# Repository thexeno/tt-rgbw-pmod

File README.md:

# tt-rgbw-pmod
An overkill PMOD to handle an RGBW LED for experimenting with the color rendering of the [thexeno/tt08-rgbw-controller](https://github.com/thexeno/tt08-rgbw-controller/ "tt08-rgbw-controller") ASIC. 
This PMOD matches with the [TinyTapeout/tt-demo-pcb](https://github.com/TinyTapeout/tt-demo-pcb "tt-demo-pcb"). These links are referred to as the "ASIC documentation".

### <p align="center"> PREVIEW: https://www.youtube.com/watch?v=X-74kIeId4A </p>

  <div align="center">

  <br>
  </div>

## Overview

This PMOD board provides high-power LED driver capabilities for the tt08-rgbw-controller ASIC, featuring four independent channels for RGBW LED control with both digital PWM and analog dimming modes.

## Pinout

### PWM inputs (inputs PMOD side, outputs ASIC side)

| Pmod    | TinyTapeout | Function        | Note                  |
|---------|-------------|-----------------|-----------------------|
| OUTPUT1 | uo[0]       | Red PWM input   | Input impedance 100 kΩ|
| OUTPUT2 | uo[1]       | Green PWM input | Input impedance 100 kΩ|
| OUTPUT3 | uo[2]       | Blue PWM input  | Input impedance 100 kΩ|
| OUTPUT4 | uo[3]       | White PWM input | Input impedance 100 kΩ|
| OUTPUT5 - 8   | uo[4:7]           | Not connected   |                       |

### Inputs ASIC side

All "INPUT" pins are disconnected on the PMOD, not used. But the ASIC and the Demoboard are using them for the SPI communication, so signals are present if probed. See ASIC documentation.

### Colorwheel Debug Port

This applies only if enabled, see ASIC documentation.

| Pmod    | TinyTapeout | Function        | Note                  |
|---------|-------------|-----------------|-----------------------|
| BIDIR1 | uio_out[0]       | CwPU register bit 0   |  |
| BIDIR2 | uio_out[1]       | CwPU register bit 1 | |
| BIDIR3 | uio_out[2]       | CwPU register bit 2  | |
| BIDIR4 | uio_out[3]       | CwPU register bit 3 | |
| BIDIR5    | uio_out[4]           | CwPU register bit 4   |                       |
| BIDIR6    | uio_out[5]           | CwPU register bit 5   |                       |
| BIDIR7    | uio_out[6]           | CwPU register bit 6   |                       |
| BIDIR8    | uio_out[7]           | CwPU register bit 7   |                       |

## Getting Started

### Quick Setup Checklist

1. Select the control mode for each color channel using jumpers JP1–JP4:
  - Jumper bridged: Analog (LED-side) dimming mode
  - Jumper open: Digital (LED-side) PWM mode
2. Verify 3.3V power is available on the Demoboard's PMOD connector.
3. Connect the RGBW Color Processor board to the Demoboard.
4. Apply external power: Connect 6–20V to J4 or J5 (minimum 5V required to activate drivers).

### Using External LEDs

To use external LEDs instead of the onboard ones, open the following jumper connections:
- R3, R4, R5, R8, R9, R10, R11, R12

### Current Adjustment

Adjust the constant-current output via resistors:
- R14 (Red channel)
- R18 (Green channel)
- R22 (Blue channel)
- R26 (White channel)

Current calculation:
- Digital dimming mode: I = 0.1V / R (default: 75 mA)
- Analog dimming mode: I = 0.2V / R (default: 150 mA)

## Operating Modes

### Digital PWM Mode (Jumper Open)
- PWM PMOD pin frequency: < 1 kHz
- Lower current consumption
- Suitable for most applications

### Analog Dimming Mode (Jumper Bridged)
- PWM PMOD pin frequency: > 10 kHz (recommended: 50 kHz)
- Higher current capability
- For continuous operation at default settings (150 mA per channel), a small heatsink is recommended:
  - Base size: 7×7 mm
  - Thermal resistance: 30–40 °C/W
 
## Debugging Features

Breakout to CwPU protocol 8-bit interface for internal registers probing. This is active only if enabled. See ASIC documentation.

## Electrical Characteristics

| Parameter                                      | Min | Typ | Max | Unit | Notes                      |
|-----------------------------------------------|-----|-----|-----|------|----------------------------|
| External supply voltage                        | 6   | 12  | 20  | V    | Required (J4 or J5)        |
| External supply current                        | -   | -   | 400 | mA  | 2W total max               |
| PMOD Logic VDD                        | 3.0   | -   | 5.0 | V  | To handle correctly analog or digital dimming detection               |
| Logic input voltage                            | -   | 3.3 | -   | V    | TTL compatible             |
| LED current (Digital mode)                     | -   | 75  | -   | mA   | Per channel, default       |
| LED current (Analog mode)                      | -   | 150 | -   | mA   | Per channel, default       |
| PWM input for Digital mode           | -   | -   | 1   | kHz  | Maximum recommended        |
| PWM input for Analog mode            | 10  | 50  | -   | kHz  | Minimum / recommended      |
| V<sub>IL</sub>                                     | -  | 0.8  | - | V  | LVTTL     |
| V<sub>IH</sub>                                       | -  | 2.0  | - | V  | LVTTL     |

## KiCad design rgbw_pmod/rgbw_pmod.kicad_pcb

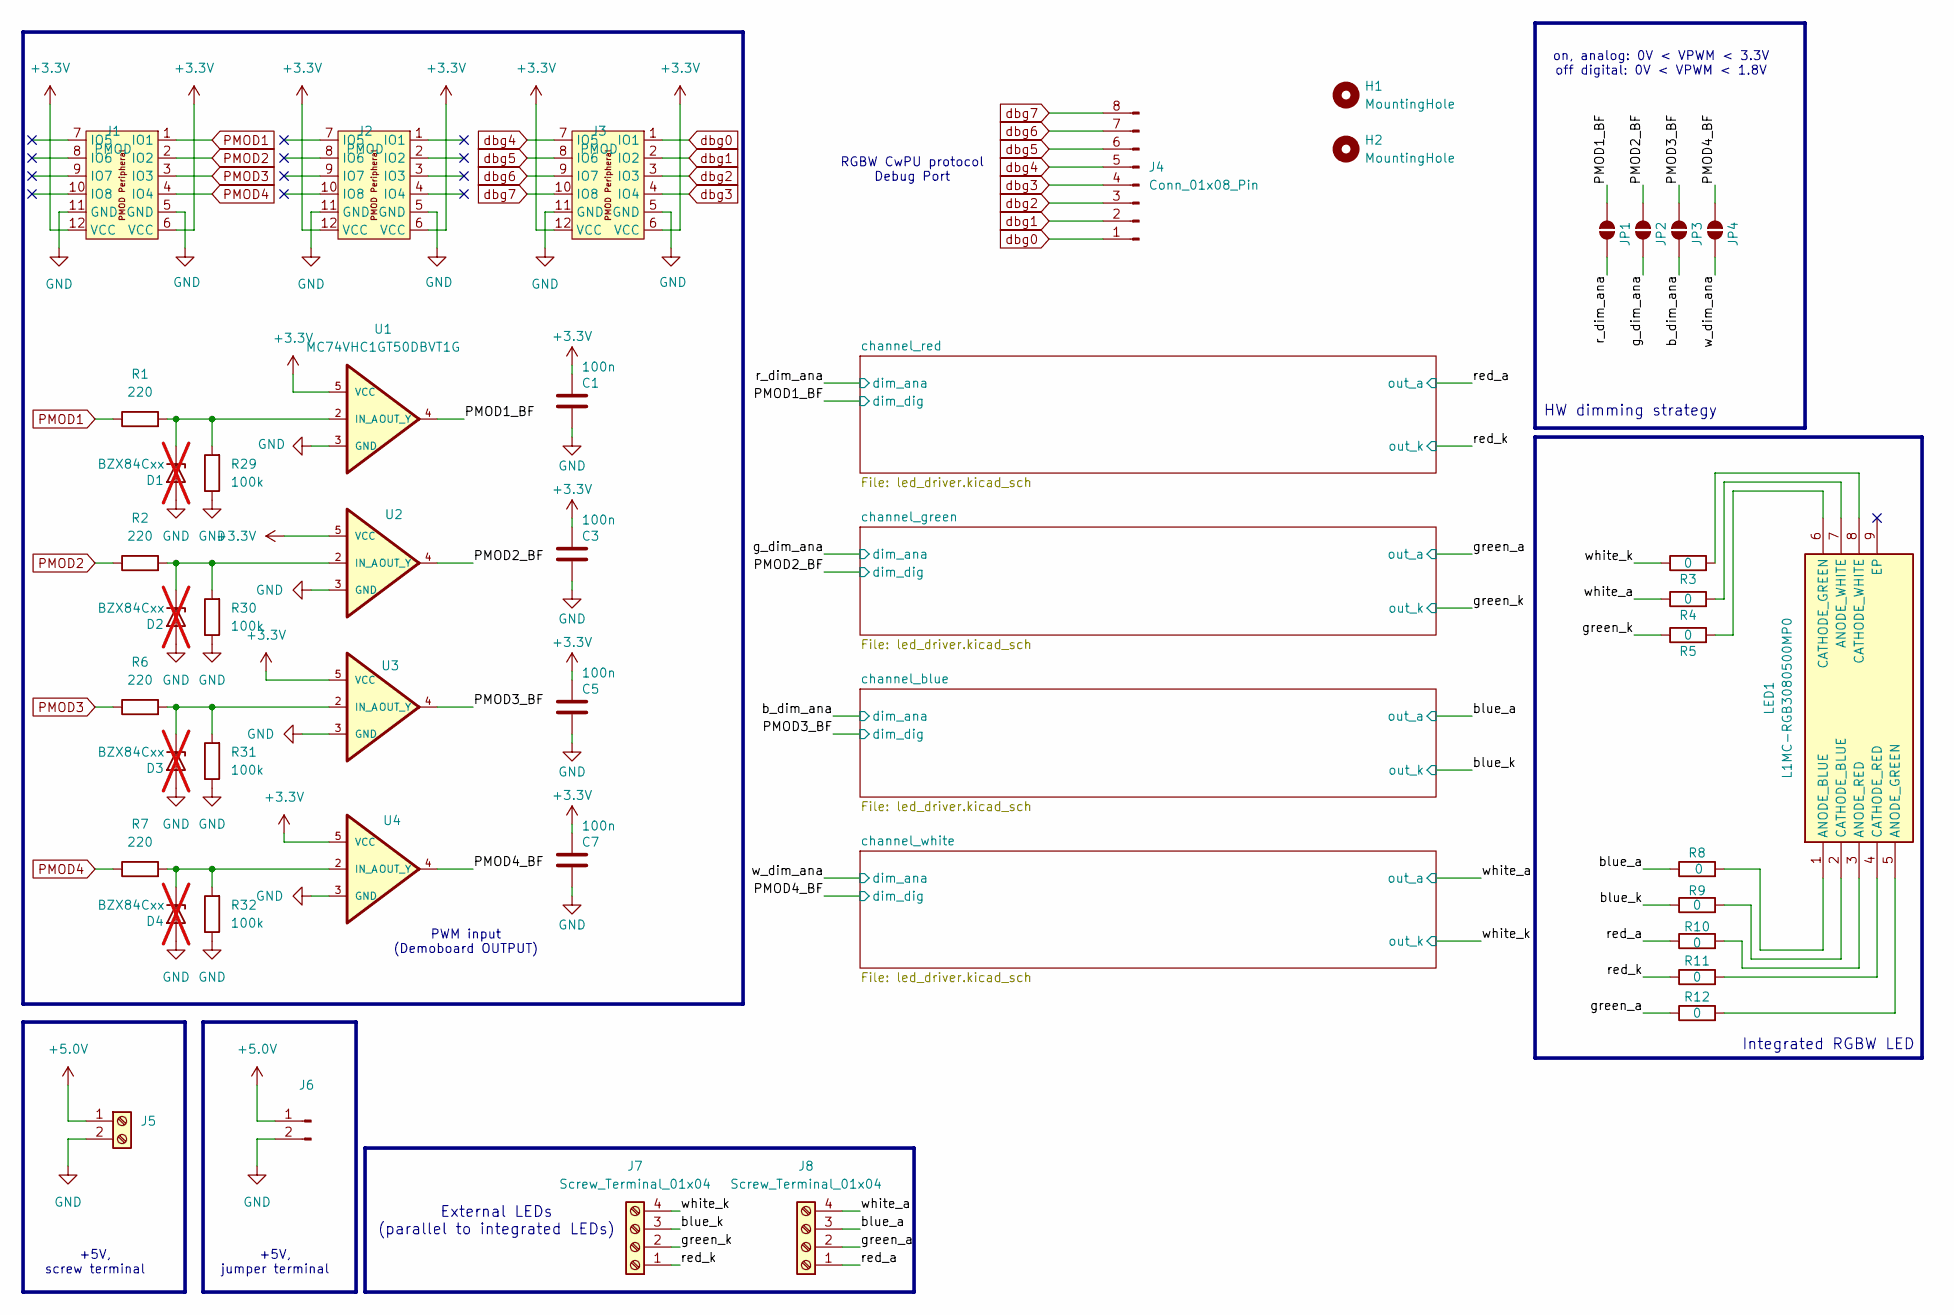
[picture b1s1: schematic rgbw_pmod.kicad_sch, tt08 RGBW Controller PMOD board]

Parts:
C1, C3, C5, C7: 100n; C_0603_1608Metric_Pad1.08x0.95mm_HandSolder
D1, D2, D3, D4: BZX84Cxx; SOT-23-3; not fitted
H1, H2: MountingHole; MountingHole_3.2mm_M3_ISO7380
J1, J2, J3: PMOD; PinHeader_2x06_P2.54mm_PMODPeriph2B; MPN 826634-6; LCSC C2935938
J4: Conn_01x08_Pin; PinHeader_1x08_P2.54mm_Vertical
J5: Screw_Terminal_01x02; TerminalBlock_Altech_AK300-2_P5.00mm
J6: Conn_01x02_Pin; PinHeader_1x02_P2.54mm_Vertical
J7, J8: Screw_Terminal_01x04; Altech_AK100_1x04_P5.00mm
JP1, JP2, JP3, JP4: SolderJumper_2_Open; SolderJumper-2_P1.3mm_Open_TrianglePad1.0x1.5mm
LED1: L1MC-RGB3080500MP0; L1MCRGB3080500MP0; Mouser Part Number 997-L1MCRGB3080500MP
R1, R2, R6, R7: 220; R_0603_1608Metric_Pad0.98x0.95mm_HandSolder
R3, R4, R5, R8, R9, R10, R11, R12: 0; R_0603_1608Metric_Pad0.98x0.95mm_HandSolder
R29, R30, R31, R32: 100k; R_0603_1608Metric_Pad0.98x0.95mm_HandSolder
U1, U2, U3, U4: MC74VHC1GT50DBVT1G; SOT95P275X110-5N; MPN MC74VHC1GT50DTT1

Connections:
+3.3V: C1.1, C3.1, C5.1, C7.1, J1.6 (VCC), J1.12 (VCC), J2.6 (VCC), J2.12 (VCC), J3.6 (VCC), J3.12 (VCC), U1.5 (VCC), U2.5 (VCC), U3.5 (VCC), U4.5 (VCC)
+5.0V: J5.1, J6.1; also elsewhere on the board
/PMOD1_BF: JP1.2 (B), U1.4 (OUT_Y); also elsewhere on the board
/PMOD2_BF: JP2.2 (B), U2.4 (OUT_Y); also elsewhere on the board
/PMOD3_BF: JP3.2 (B), U3.4 (OUT_Y); also elsewhere on the board
/PMOD4_BF: JP4.2 (B), U4.4 (OUT_Y); also elsewhere on the board
/b_dim_ana: JP3.1 (A); also elsewhere on the board
/blue_a: J8.3, R8.1; also elsewhere on the board
/blue_k: J7.3, R9.1; also elsewhere on the board
/g_dim_ana: JP2.1 (A); also elsewhere on the board
/green_a: J8.2, R12.1; also elsewhere on the board
/green_k: J7.2, R5.1; also elsewhere on the board
/r_dim_ana: JP1.1 (A); also elsewhere on the board
/red_a: J8.1, R10.1; also elsewhere on the board
/red_k: J7.1, R11.1; also elsewhere on the board
/w_dim_ana: JP4.1 (A); also elsewhere on the board
/white_a: J8.4, R4.1; also elsewhere on the board
/white_k: J7.4, R3.1; also elsewhere on the board
GND: C1.2, C3.2, C5.2, C7.2, D1.1 (A), D2.1 (A), D3.1 (A), D4.1 (A), J1.5 (GND), J1.11 (GND), J2.5 (GND), J2.11 (GND), J3.5 (GND), J3.11 (GND), J5.2, J6.2, R29.1, R30.1, R31.1, R32.1, U1.3 (GND), U2.3 (GND), U3.3 (GND), U4.3 (GND); also elsewhere on the board
unnamed: D1.3 (K), R1.2, R29.2, U1.2 (IN_A)
unnamed: D2.3 (K), R2.2, R30.2, U2.2 (IN_A)
unnamed: D3.3 (K), R6.2, R31.2, U3.2 (IN_A)
unnamed: D4.3 (K), R7.2, R32.2, U4.2 (IN_A)
unnamed: LED1.1 (ANODE_BLUE), R8.2
unnamed: LED1.5 (ANODE_GREEN), R12.2
unnamed: LED1.3 (ANODE_RED), R10.2
unnamed: LED1.7 (ANODE_WHITE), R4.2
unnamed: LED1.2 (CATHODE_BLUE), R9.2
unnamed: LED1.6 (CATHODE_GREEN), R5.2
unnamed: LED1.4 (CATHODE_RED), R11.2
unnamed: LED1.8 (CATHODE_WHITE), R3.2
PMOD1: J1.1 (IO1), R1.1
PMOD2: J1.2 (IO2), R2.1
PMOD3: J1.3 (IO3), R6.1
PMOD4: J1.4 (IO4), R7.1
dbg0: J3.1 (IO1), J4.1
dbg1: J3.2 (IO2), J4.2
dbg2: J3.3 (IO3), J4.3
dbg3: J3.4 (IO4), J4.4
dbg4: J3.7 (IO5), J4.5
dbg5: J3.8 (IO6), J4.6
dbg6: J3.9 (IO7), J4.7
dbg7: J3.10 (IO8), J4.8

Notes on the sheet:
on, analog: 0V < VPWM < 3.3V off digital: 0V < VPWM < 1.8V
Integrated RGBW LED
+5V, screw terminal
External LEDs (parallel to integrated LEDs)
PWM input (Demoboard OUTPUT)
+5V, jumper terminal
HW dimming strategy
RGBW CwPU protocol Debug Port

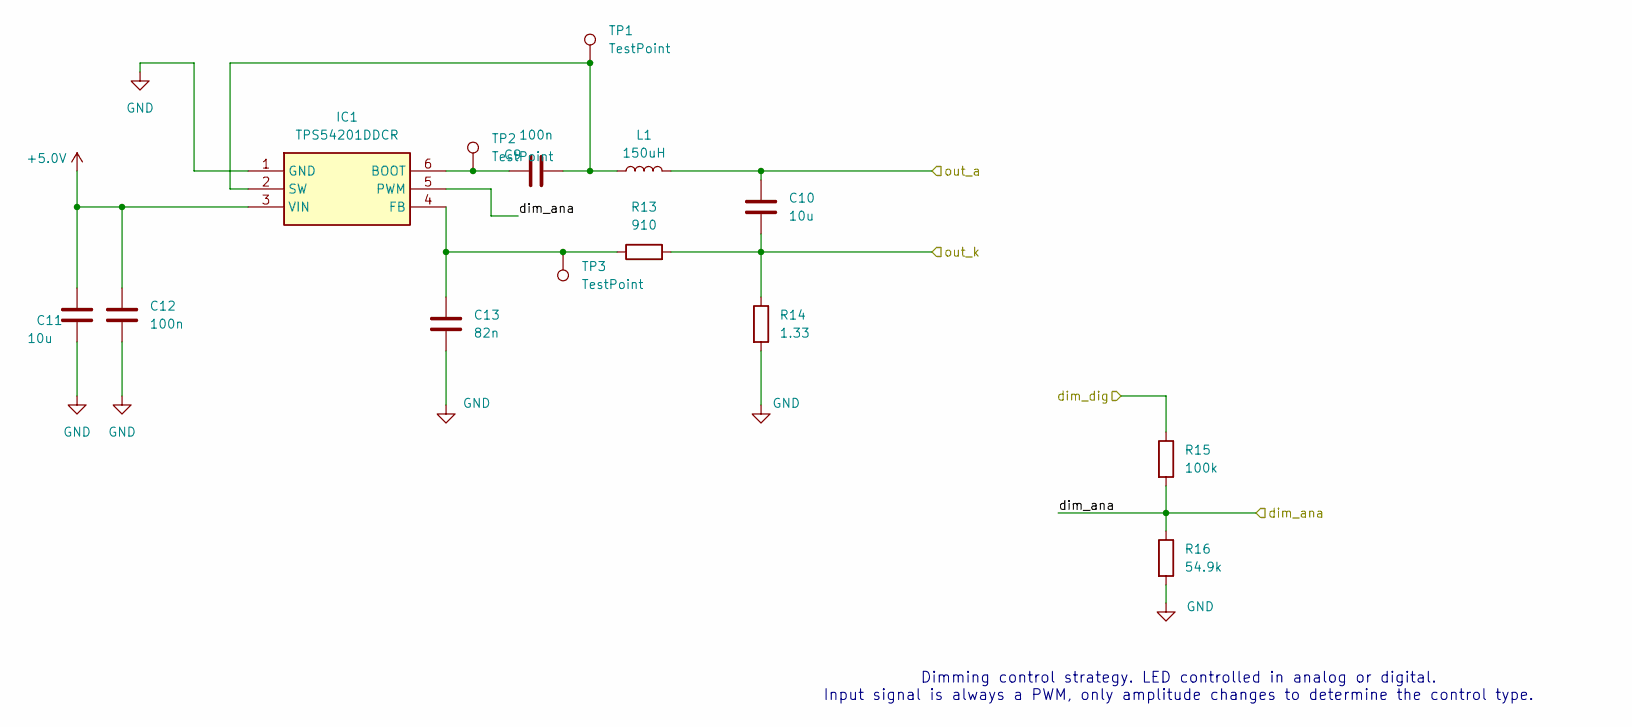
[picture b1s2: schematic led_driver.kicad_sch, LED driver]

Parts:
C9, C12: 100n; C_0603_1608Metric_Pad1.08x0.95mm_HandSolder
C10, C11: 10u; C_0805_2012Metric_Pad1.18x1.45mm_HandSolder
C13: 82n; C_0603_1608Metric_Pad1.08x0.95mm_HandSolder
IC1: TPS54201DDCR; SOT95P280X110-6N; Mouser Part Number 595-TPS54201DDCR
L1: 150uH; IND_BOURNS_SRR5028
R13: 910; R_0603_1608Metric_Pad0.98x0.95mm_HandSolder
R14: 1.33; R_0805_2012Metric_Pad1.20x1.40mm_HandSolder
R15: 100k; R_0603_1608Metric_Pad0.98x0.95mm_HandSolder
R16: 54.9k; R_0603_1608Metric_Pad0.98x0.95mm_HandSolder
TP1: TestPoint; TestPoint_Pad_D1.0mm
TP2, TP3: TestPoint; TestPoint_Keystone_5015_Micro_Mini

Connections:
+5.0V: C11.1, C12.1, IC1.3 (VIN); also elsewhere on the board
/PMOD1_BF: R15.1; also elsewhere on the board
/r_dim_ana: IC1.5 (PWM), R15.2, R16.1; also elsewhere on the board
/red_a: C10.1, L1.2; also elsewhere on the board
/red_k: C10.2, R13.2, R14.1; also elsewhere on the board
GND: C11.2, C12.2, C13.1, IC1.1 (GND), R14.2, R16.2; also elsewhere on the board
unnamed: C9.1, IC1.6 (BOOT), TP2.1
unnamed: C13.2, IC1.4 (FB), R13.1, TP3.1
unnamed: C9.2, IC1.2 (SW), L1.1, TP1.1

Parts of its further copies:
C14, C17, C19, C22, C24, C27: 100n; C_0603_1608Metric_Pad1.08x0.95mm_HandSolder
C15, C16, C20, C21, C25, C26: 10u; C_0805_2012Metric_Pad1.18x1.45mm_HandSolder
C18, C23, C28: 82n; C_0603_1608Metric_Pad1.08x0.95mm_HandSolder
IC2, IC3, IC4: TPS54201DDCR; SOT95P280X110-6N; Mouser Part Number 595-TPS54201DDCR
L2, L3, L4: 150uH; IND_BOURNS_SRR5028
R17, R21, R25: 910; R_0603_1608Metric_Pad0.98x0.95mm_HandSolder
R18, R22, R26: 1.33; R_0805_2012Metric_Pad1.20x1.40mm_HandSolder
R19, R23, R27: 100k; R_0603_1608Metric_Pad0.98x0.95mm_HandSolder
R20, R24, R28: 54.9k; R_0603_1608Metric_Pad0.98x0.95mm_HandSolder
TP5, TP9, TP13: TestPoint; TestPoint_Pad_D1.0mm
TP6, TP7, TP10, TP11, TP14, TP15: TestPoint; TestPoint_Keystone_5015_Micro_Mini

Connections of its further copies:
+5.0V: C16.1, C17.1, C21.1, C22.1, C26.1, C27.1, IC2.3 (VIN), IC3.3 (VIN), IC4.3 (VIN); also elsewhere on the board
/PMOD2_BF: R19.1; also elsewhere on the board
/PMOD3_BF: R23.1; also elsewhere on the board
/PMOD4_BF: R27.1; also elsewhere on the board
/b_dim_ana: IC3.5 (PWM), R23.2, R24.1; also elsewhere on the board
/blue_a: C20.1, L3.2; also elsewhere on the board
/blue_k: C20.2, R21.2, R22.1; also elsewhere on the board
/g_dim_ana: IC2.5 (PWM), R19.2, R20.1; also elsewhere on the board
/green_a: C15.1, L2.2; also elsewhere on the board
/green_k: C15.2, R17.2, R18.1; also elsewhere on the board
/w_dim_ana: IC4.5 (PWM), R27.2, R28.1; also elsewhere on the board
/white_a: C25.1, L4.2; also elsewhere on the board
/white_k: C25.2, R25.2, R26.1; also elsewhere on the board
GND: C16.2, C17.2, C18.1, C21.2, C22.2, C23.1, C26.2, C27.2, C28.1, IC2.1 (GND), IC3.1 (GND), IC4.1 (GND), R18.2, R20.2, R22.2, R24.2, R26.2, R28.2; also elsewhere on the board
unnamed: C14.1, IC2.6 (BOOT), TP6.1
unnamed: C18.2, IC2.4 (FB), R17.1, TP7.1
unnamed: C14.2, IC2.2 (SW), L2.1, TP5.1
unnamed: C19.1, IC3.6 (BOOT), TP10.1
unnamed: C23.2, IC3.4 (FB), R21.1, TP11.1
unnamed: C19.2, IC3.2 (SW), L3.1, TP9.1
unnamed: C24.1, IC4.6 (BOOT), TP14.1
unnamed: C28.2, IC4.4 (FB), R25.1, TP15.1
unnamed: C24.2, IC4.2 (SW), L4.1, TP13.1

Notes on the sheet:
Dimming control strategy. LED controlled in analog or digital. Input signal is always a PWM, only amplitude changes to determine the control type.

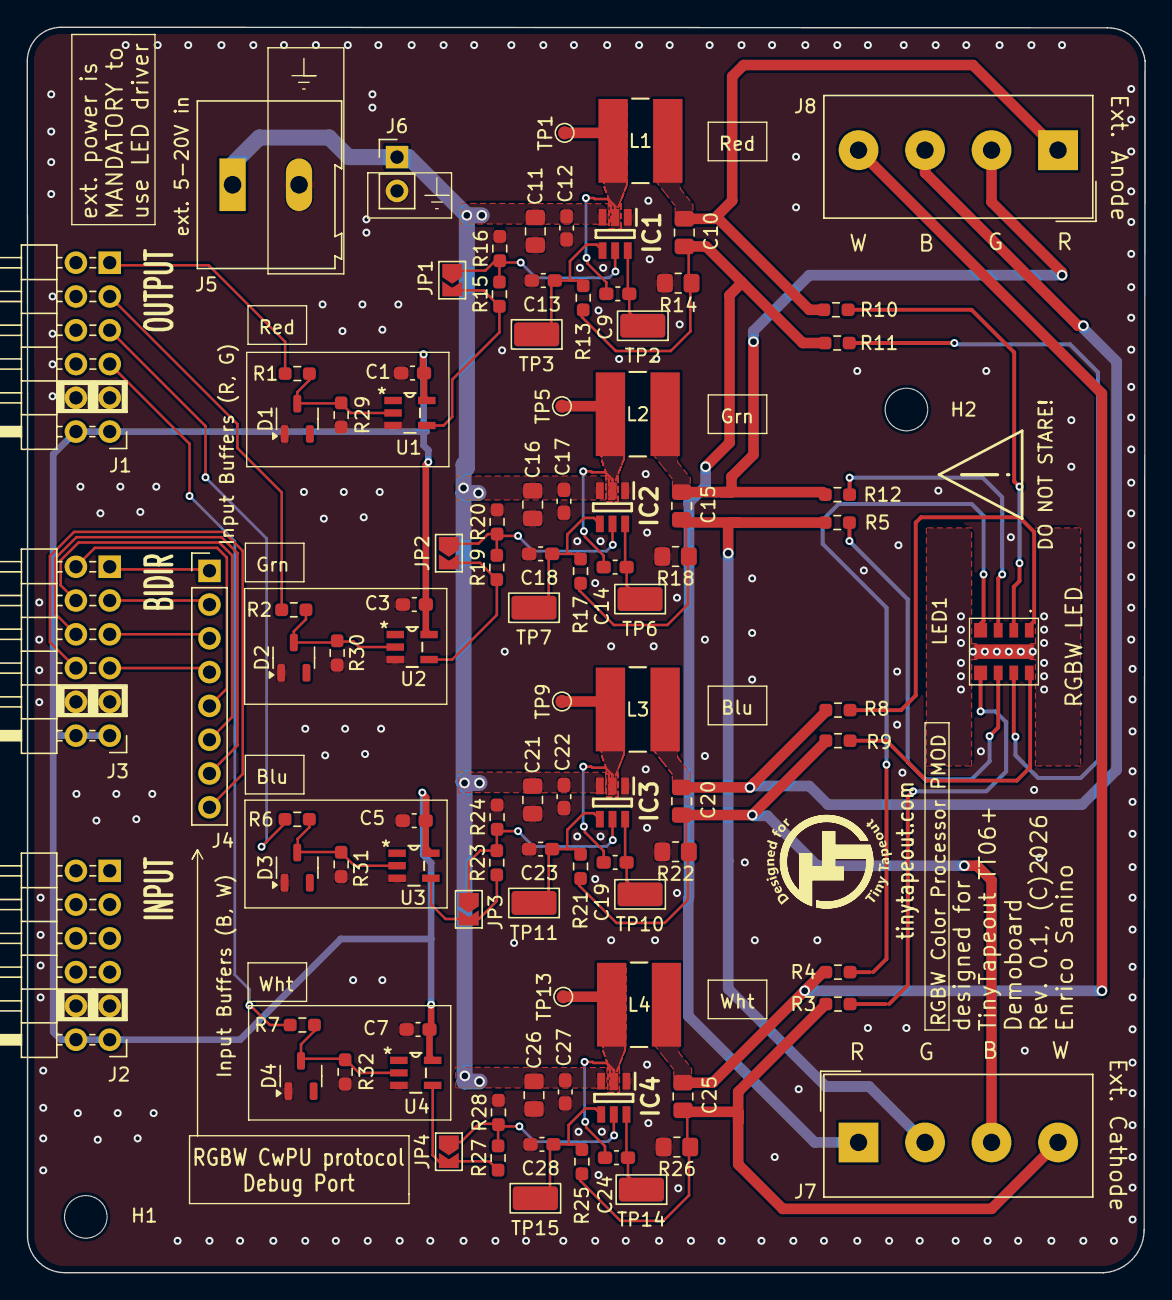
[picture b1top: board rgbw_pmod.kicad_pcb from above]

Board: 2 copper layers, 84.0 x 93.6 mm, 101 parts (1 on the bottom side), 55 nets.

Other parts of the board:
LOGO1: PMOD_LOGO; TT_PMOD_Logo_7mm
LOGO2: KiCad-Logo2_5mm_SilkScreen

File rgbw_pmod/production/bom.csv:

Designator,Footprint,Quantity,Value,LCSC Part #
"C1, C12, C14, C17, C19, C22, C24, C27, C3, C5, C7, C9",0603,12,100n,
"C10, C11, C15, C16, C20, C21, C25, C26",0805,8,10u,
"C13, C18, C23, C28",0603,4,82n,
"C2, C4, C6, C8",0603,4,10n,
"D1, D2, D3, D4",SOT-23-3,4,BZX84Cxx,
"IC1, IC2, IC3, IC4",SOT95P280X110-6N,4,TPS54201DDCR,
"J1, J2, J3",PinHeader_2x06_P2.54mm_PMODPeriph2B,3,PMOD,C492434
J4,PinHeader_1x08_P2.54mm_Vertical,1,Conn_01x08_Pin,
J5,TerminalBlock_Altech_AK300-2_P5.00mm,1,Screw_Terminal_01x02,
J6,PinHeader_1x02_P2.54mm_Vertical,1,Conn_01x02_Pin,
"J7, J8",Altech_AK100_1x04_P5.00mm,2,Screw_Terminal_01x04,
"L1, L2, L3, L4",IND_BOURNS_SRR5028,4,150uH,
LED1,L1MCRGB3080500MP0,1,L1MC-RGB3080500MP0,
"R1, R2, R6, R7",0603,4,220,
"R10, R11, R12, R3, R4, R5, R8, R9",0603,8,0,
"R13, R17, R21, R25",0603,4,910,
"R14, R18, R22, R26",0805,4,1.33,
"R15, R19, R23, R27",0603,4,100k,
"R16, R20, R24, R28",0603,4,54.9k,
"TP1, TP10, TP11, TP13, TP14, TP15, TP2, TP3, TP5, TP6, TP7, TP9",TestPoint_Keystone_5015_Micro_Mini,12,TestPoint,
"U1, U2, U3, U4",SOT95P275X110-5N,4,MC74VHC1GT50DBVT1G,MC74VHC1GT50DTT1

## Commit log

2026-02-05 Expand README with setup and operational details
    Added tempoerary overview, pinout, setup instructions, operating modes, electrical characteristics, and empty license information
2026-02-05 Add images and update README with board illustration
2026-02-05 Update README to correct image path
2026-02-05 image path correction
2026-02-05 Linking project external references
2026-02-09 Update README with new pinout and debugging features (incomplete)
    Added additional PWM inputs and Colorwheel Debug Port information to the README.
2026-02-09 Update README with ASIC documentation note
    Added note about ASIC documentation for Colorwheel Debug Port.
2026-02-09 Delete License section from README
    Remove placeholder license section from README
2026-02-09 Enhance README with demo video and image
    Added a link to a demo video and an image to the README.
2026-02-10 new images and resize
2026-02-10 Fix video link and update image in README
    Updated video link and image in README.md
2026-02-10 Revise video preview in README.md
    Updated video preview section with new images and removed duplicate link.
2026-02-10 Enhance README formatting and image display
    Updated README to improve formatting and add image alignment.
2026-02-10 Clarify ASIC documentation and debugging features
    Updated README to clarify ASIC documentation references and debugging features.
2026-02-10 KiCad design files and libs
2026-02-10 remaining KiCad files

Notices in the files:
rgbw_pmod/rgbw_pmod.kicad_pcb:
Rev. 0.1, (C)2026
